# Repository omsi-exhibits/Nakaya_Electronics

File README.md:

# Nakaya Electronics Details

## Theory of Operation
The Nakaya Electronics are composed of a mainboard that a ItsyBitsy32u4 microcontroller is socketed into. The mainboard connects to 4 sensor boards and 4 led light boards. Each Sensor board has 12 reed switches that are read by 2 shift in registers.  Each light board has a 24 rgbw neoPixel ring attached. The software for the microcontroller checks each Sensor board for the snow pucks that correspond as a correct answer to the description of the snow for that section. Each section has 2 answers that work. When a correct answer is placed in the slot the light board fades in a light in the center of the snowflake and the mainboard triggers a sound. When the piece is removed the light fades out.  

The way the software works is that there are Sensor object instances that each loop read the sensor data store it in a data object
and then there is some logic that checks wether or not a correct sensor has been just places or has been just removed. This in turn
calls the led modules trigger functions that begin fading in or fading out.
The same logic is also responsible to trigger sounds
to play when the pieces are inserted or removed. If all 4 of the same type of snowflake are in the correct slots a victory sound will play.

### Updating software
The software is built using platformio. You can use Arduino IDE by copying the src folder
and renaming it to Nakaya and renaming the main.cpp file to Nakaya.ino. This will allow
you to use Arduino to make modifications. You will need to install any missing libraries
through the Arduino Library manager.

### Project File Organization
- docs : documentation and pictures
- src : source code
- eagle : pcb files
- examples_tests : code to help test and trouble shoot
- audio_assets : wavTrigger files
- readme.md : basic project info its the file you are reading
- docs/Nakaya BOM v2.xls (BOM is on sheet 2)
- some other directories are used by platformio and vscode

### Sensor Board
 10” by 10” square board size, sensing distance at 5/8" and less. 
- Shift Register x 2
- Reed Switches
- Phoenix Connectors
- Spacers - Between board and Milkplex
- Stand Offs - Between board and bottom plate

## Main board
- reverse voltage protection
- phoenix connectors
- MCU is Adafruit ItsyBitsy32u4

### Audio 
The wavTrigger is the audio player that interfaces with the main board via a 5pin rectangular connector. KK254 series molex connector.
This connector carries a serial signal over TX and RX lines. The connector also has 5v and gnd to power the board. The wavTrigger needs a pad solder birdged to allow for power intake from the serial input connector.

Software wise an AudioOut object is used to trigger sounds from the main code. It has a private instance of wavTrigger that is the hardware module that
plays wav files. The wavTrigger library has a line un-commented to allow interfacing via the hardware Serial1. The audio files are stereo wav files. 

### Game Pieces
- Each set will have 8 game pucks. Each game puck will have 1 more magnet then the
previous piece. So 1 + 2 +3 +4 +5 +6 +7 +8 = 36 magnets per set.
3 sets total = 108 magnets.
- The sensors count how many magnets are in the game piece to determine what
piece they are. 
- Each Sensor section can have 2 corresponding game pieces that trigger a success animation.

## Shift Registers

74hc165 inputs are enabled by a low level at the shift/load input.
clocking is accomplished by a low-to-high transition of the clock (CLK) input
while SH/LD is held high, and CLK INH is held low. (In my design CLK INH is
tied to ground via a trace)

Parallel load is inhibited when SH/LD is held high. While SH/LD is low the parallel
inputs to the register are enabled.

The SN74HC165 I am using needs clock to pulse from LOW to HIGH. Opposite of arduino
shiftIn().

### The Minimal Viable Product functions
- Scan the sensors every timeStep interval & insert results into DataObject
- Update Data that holds sensor results
- Run logic on Data 
- - If a corresponding puck is detected, Trigger LedModule leds to FadeIn
- - If puck is removed since lastStep Trigger LedModule leds to FadeOut

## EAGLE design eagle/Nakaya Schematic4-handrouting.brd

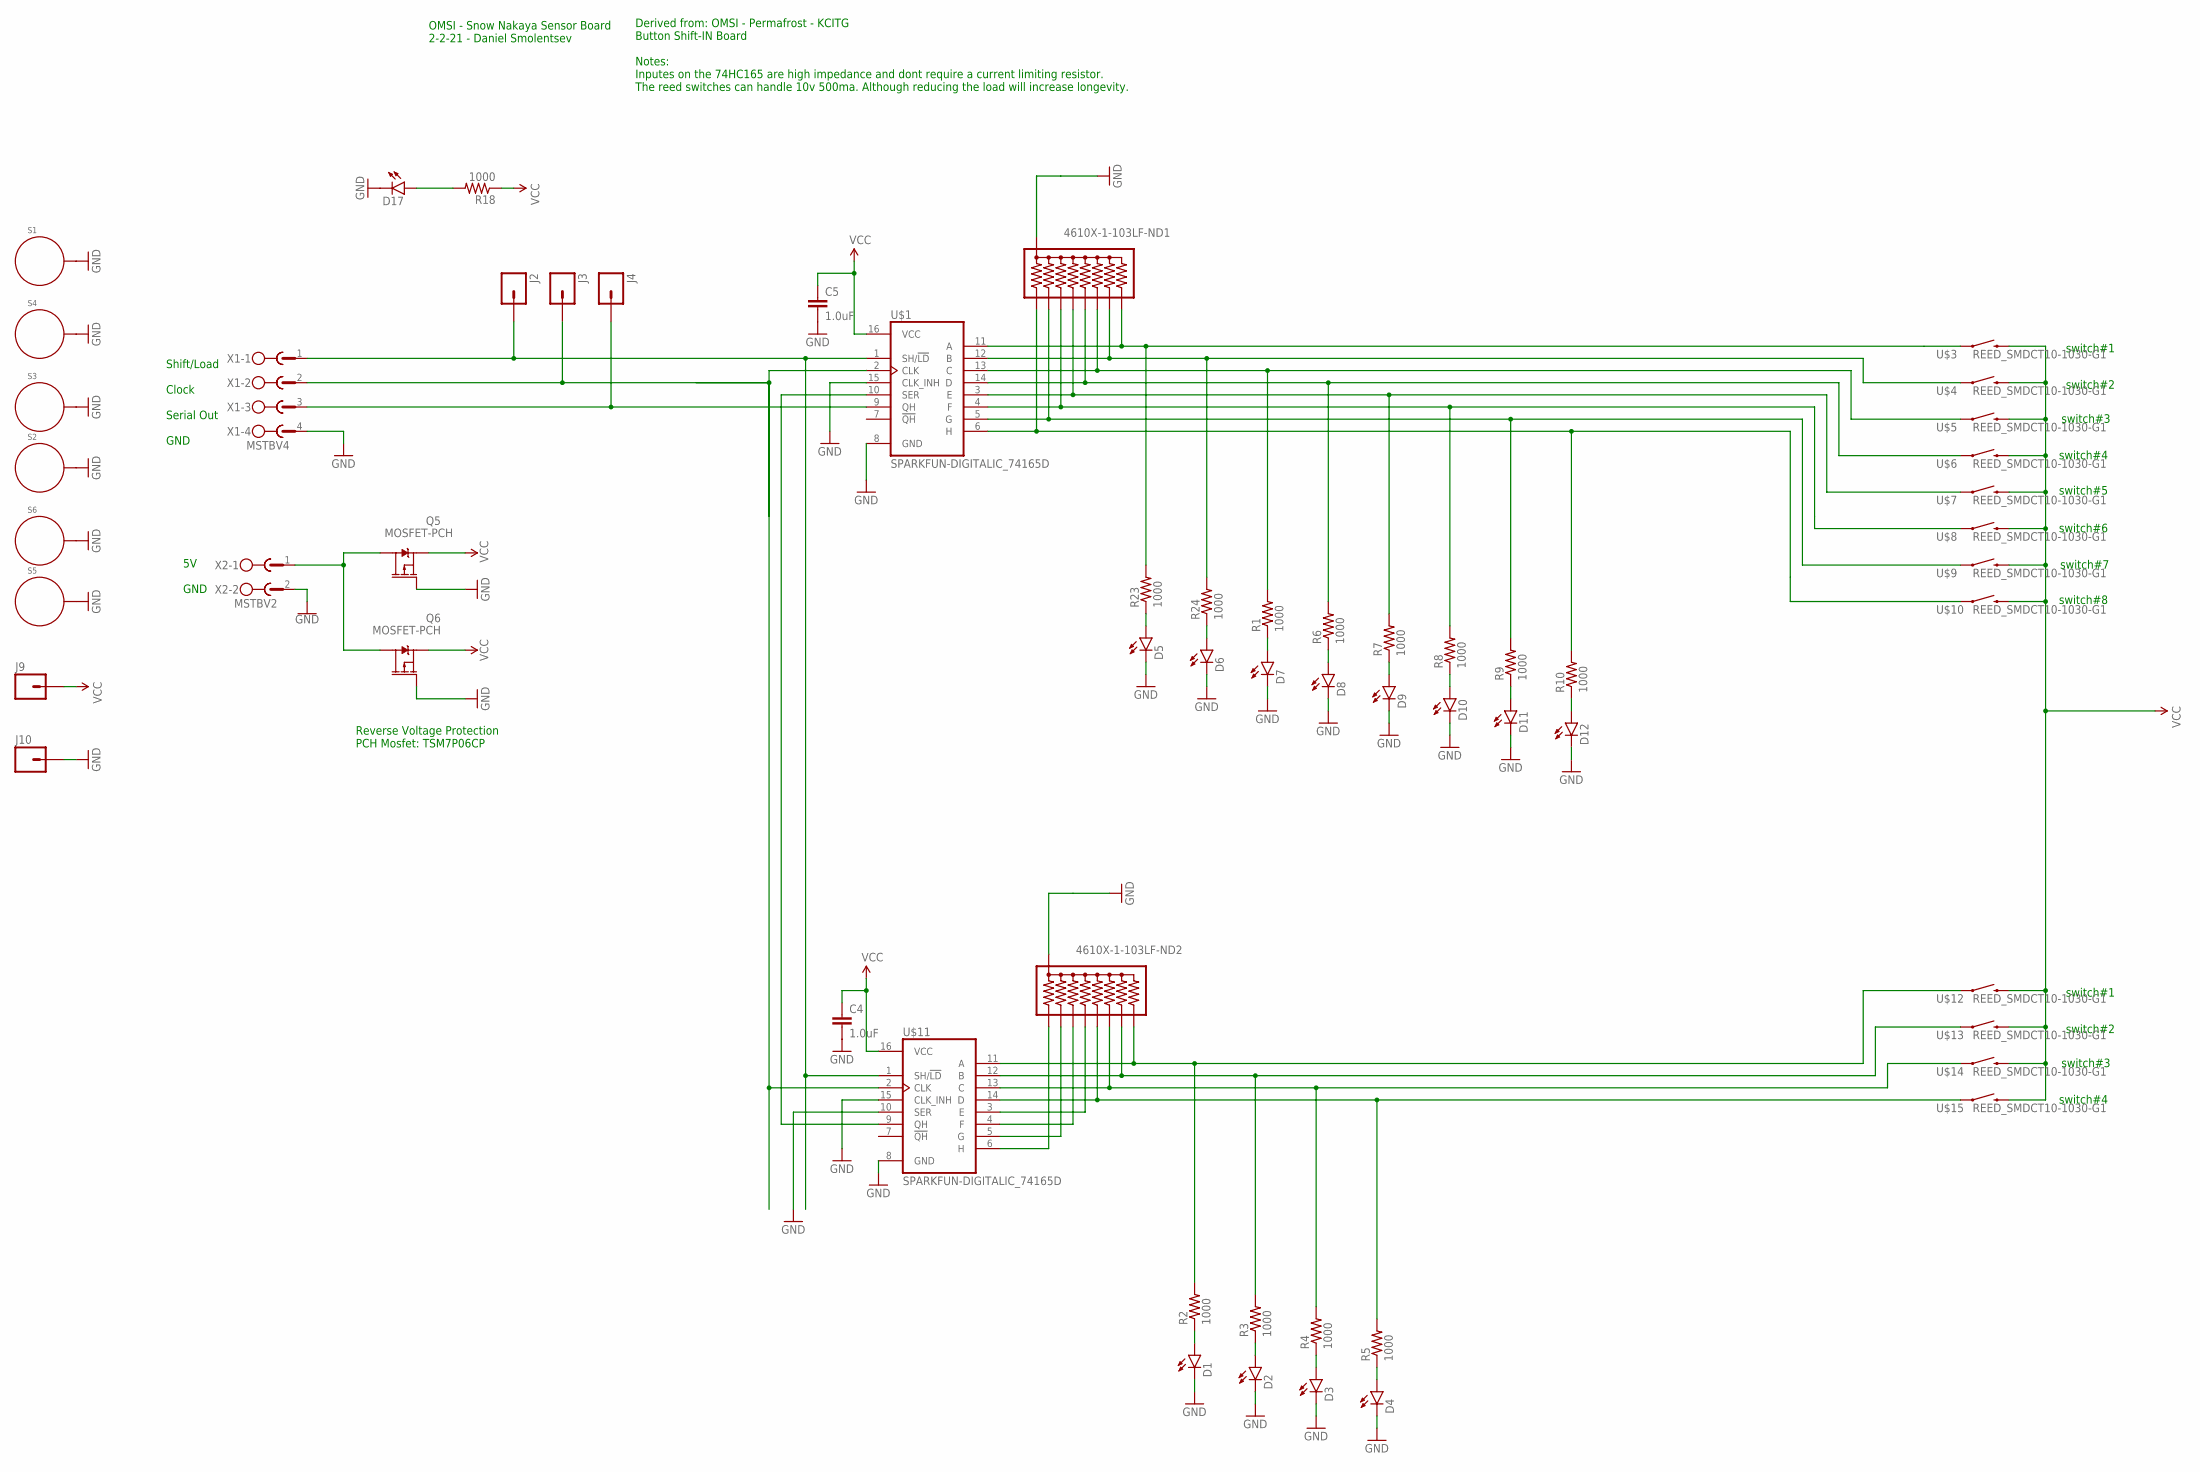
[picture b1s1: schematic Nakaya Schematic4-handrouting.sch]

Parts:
4610X-1-103LF-ND1, 4610X-1-103LF-ND2: RPACK-BUSSED-8-SIP-PTH-8; RPACK-SIP-PTH-8
C4, C5: 1.0uF; SPARKFUN-CAPACITORS_0805
D1, D2, D3, D4, D5, D6, D7, D8, D9, D10, D11, D12, D17: SPARKFUN-LED_LED1206; SPARKFUN-LED_LED-1206
J2, J3, J4, J9, J10: SPARKFUN-CONNECTORS_M01PTH_NO_SILK_YES_STOP; SPARKFUN-CONNECTORS_1X01_NO_SILK
Q5, Q6: MOSFET-PCH; DPAK
R1, R2, R3, R4, R5, R6, R7, R8, R9, R10, R18, R23, R24: 1000; SPARKFUN-PASSIVES_0805:1
S1, S2, S3, S4, S5, S6: STANDOFF_ELECTRICAL.18"; STANDOFF_ELECTRIC_#8_OVERSIZED
U$1, U$11: SPARKFUN-DIGITALIC_74165D; SPARKFUN-DIGITALIC_SO16
U$3, U$4, U$5, U$6, U$7, U$8, U$9, U$10, U$12, U$13, U$14, U$15: REED_SMDCT10-1030-G1; REED_SMD_2
X1: MSTBV4
X2: MSTBV2

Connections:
CLK: J3.1, U$1.2 (CLK), U$11.2 (CLK), X1.2
GND: 4610X-1-103LF-ND1.P$1 (1), 4610X-1-103LF-ND2.P$1 (1), C4.2, C5.2, D1.C, D2.C, D3.C, D4.C, D5.C, D6.C, D7.C, D8.C, D9.C, D10.C, D11.C, D12.C, D17.C, J10.1, Q5.1 (G), Q6.1 (G), S1.P$1, S2.P$1, S3.P$1, S4.P$1, S5.P$1, S6.P$1, U$1.8 (GND), U$1.15 (CLK_INH), U$11.8 (GND), U$11.10 (SER), U$11.15 (CLK_INH), X1.4, X2.2
LD: J2.1, U$1.1 (SH/!LD), U$11.1 (SH/!LD), X1.1
unnamed: 4610X-1-103LF-ND2.P$7 (7), R4.2, U$11.13 (C), U$14.3 (1)
unnamed: 4610X-1-103LF-ND2.P$6 (6), R5.2, U$11.14 (D), U$15.3 (1)
unnamed: D17.A, R18.2
unnamed: 4610X-1-103LF-ND1.P$4 (4), R8.2, U$1.4 (F), U$8.3 (1)
unnamed: Q5.4 (D), Q6.4 (D), X2.1
unnamed: 4610X-1-103LF-ND1.P$3 (3), R9.2, U$1.5 (G), U$9.3 (1)
unnamed: 4610X-1-103LF-ND1.P$2 (2), R10.2, U$1.6 (H), U$10.3 (1)
unnamed: D5.A, R23.1
unnamed: 4610X-1-103LF-ND2.P$8 (8), R3.2, U$11.12 (B), U$13.3 (1)
unnamed: D7.A, R1.1
unnamed: D6.A, R24.1
unnamed: D1.A, R2.1
unnamed: D8.A, R6.1
unnamed: D2.A, R3.1
unnamed: 4610X-1-103LF-ND2.P$9 (9), R2.2, U$11.11 (A), U$12.3 (1)
unnamed: D3.A, R4.1
unnamed: D4.A, R5.1
unnamed: D9.A, R7.1
unnamed: 4610X-1-103LF-ND2.P$5 (5), U$11.3 (E)
unnamed: 4610X-1-103LF-ND2.P$4 (4), U$11.4 (F)
unnamed: 4610X-1-103LF-ND2.P$3 (3), U$11.5 (G)
unnamed: D10.A, R8.1
unnamed: 4610X-1-103LF-ND2.P$2 (2), U$11.6 (H)
unnamed: D11.A, R9.1
unnamed: D12.A, R10.1
unnamed: 4610X-1-103LF-ND1.P$9 (9), R23.2, U$1.11 (A), U$3.3 (1)
unnamed: 4610X-1-103LF-ND1.P$8 (8), R24.2, U$1.12 (B), U$4.3 (1)
unnamed: 4610X-1-103LF-ND1.P$7 (7), R1.2, U$1.13 (C), U$5.3 (1)
unnamed: 4610X-1-103LF-ND1.P$6 (6), R6.2, U$1.14 (D), U$6.3 (1)
unnamed: 4610X-1-103LF-ND1.P$5 (5), R7.2, U$1.3 (E), U$7.3 (1)
QH: J4.1, U$1.9 (QH), X1.3
SER: U$1.10 (SER), U$11.9 (QH)
VCC: C4.1, C5.1, J9.1, Q5.3 (S), Q6.3 (S), R18.1, U$1.16 (VCC), U$3.4 (2), U$4.4 (2), U$5.4 (2), U$6.4 (2), U$7.4 (2), U$8.4 (2), U$9.4 (2), U$10.4 (2), U$11.16 (VCC), U$12.4 (2), U$13.4 (2), U$14.4 (2), U$15.4 (2)

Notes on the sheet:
Derived from: OMSI - Permafrost - KCITG Button Shift-IN Board Notes: Inputes on the 74HC165 are high impedance and dont require a current limiting resistor. The reed switches can handle 10v 500ma. Although reducing the load will increase longevity.
switch#1
switch#2
switch#3
switch#4
switch#5
switch#6
switch#7
switch#8
Shift/Load Clock Serial Out GND
Reverse Voltage Protection PCH Mosfet: TSM7P06CP
5V GND
OMSI - Snow Nakaya Sensor Board 2-2-21 - Daniel Smolentsev

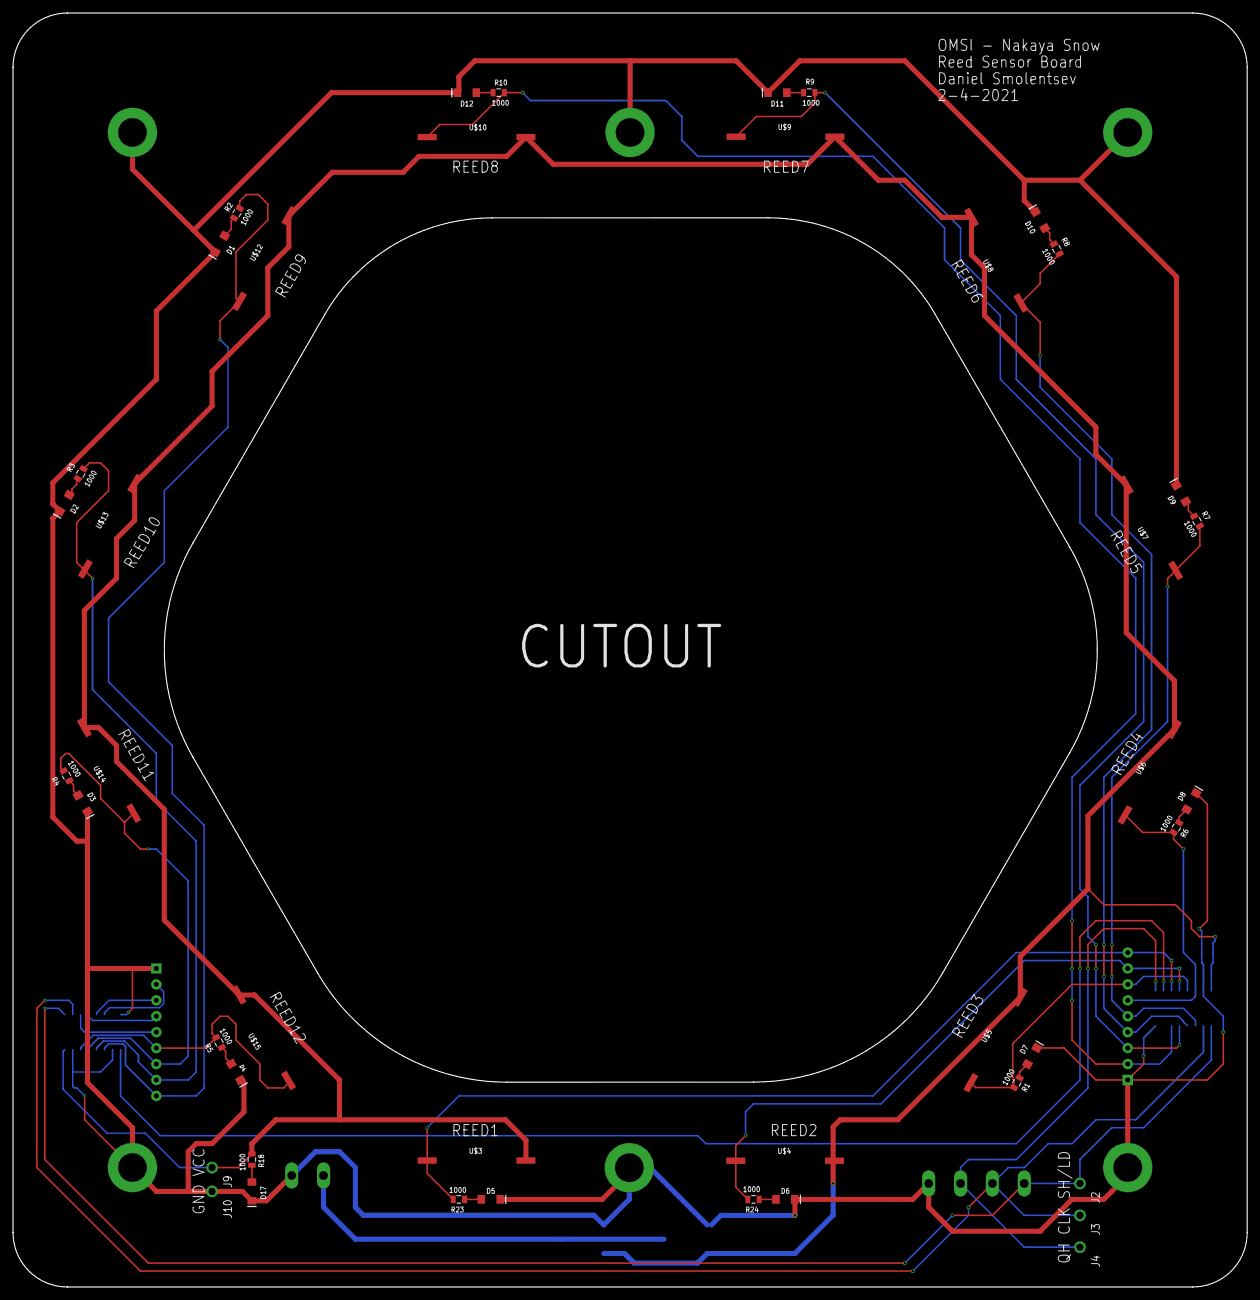
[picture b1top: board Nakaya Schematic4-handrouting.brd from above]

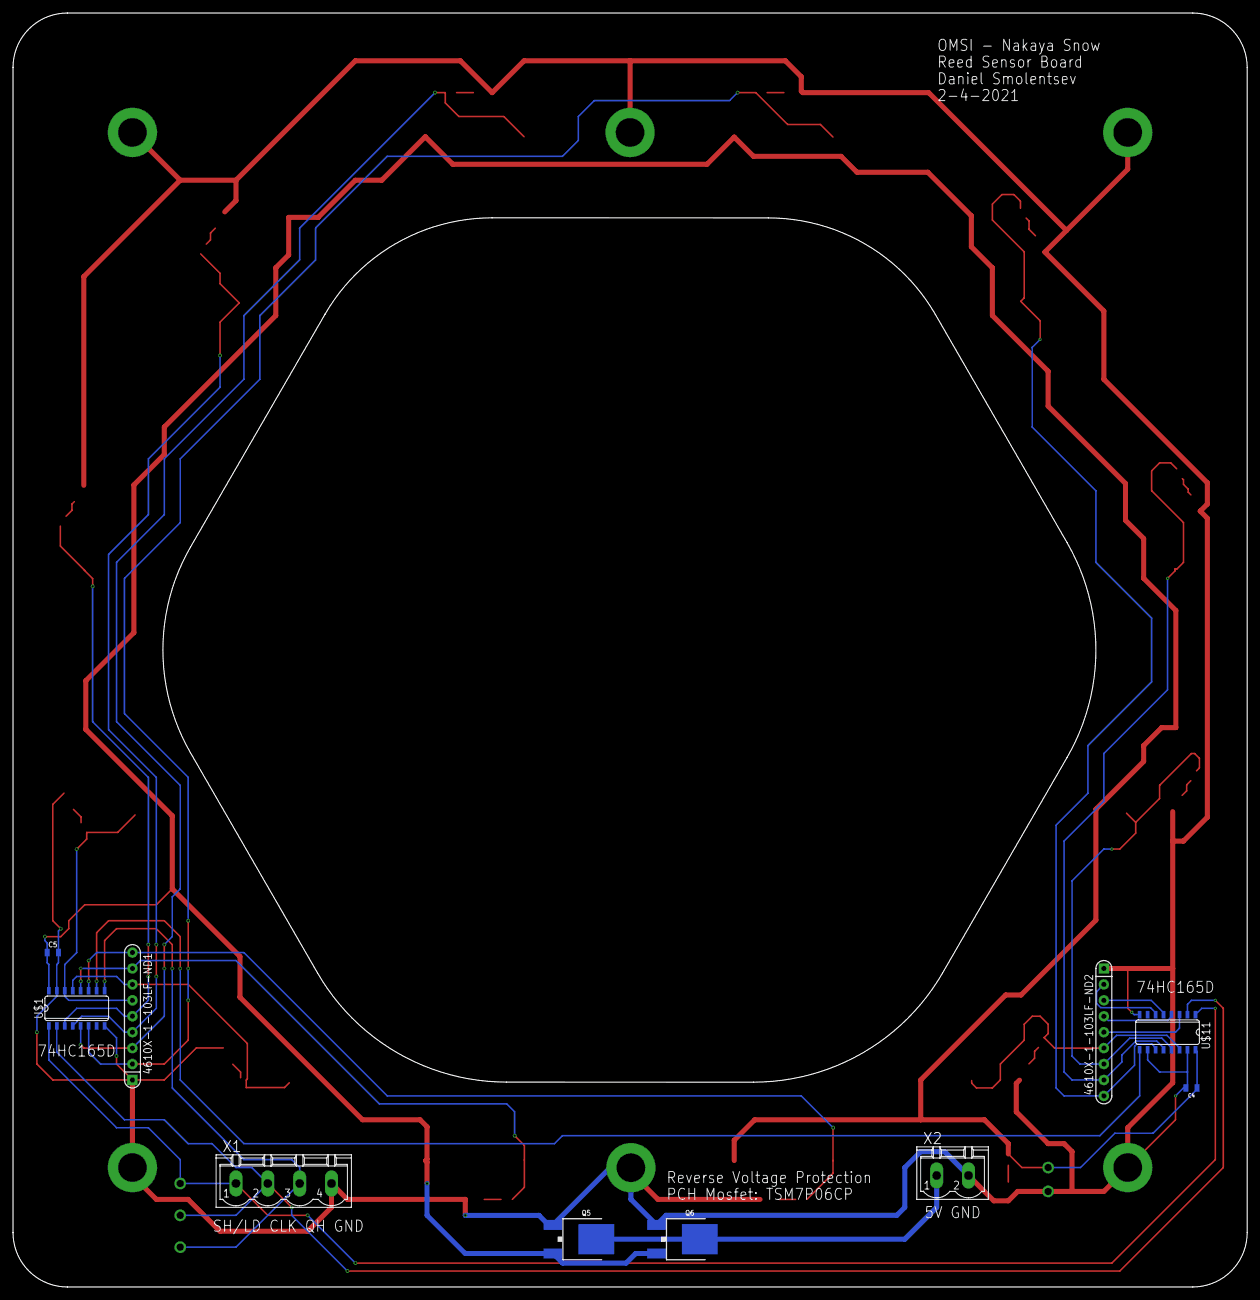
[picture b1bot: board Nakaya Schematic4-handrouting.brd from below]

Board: 2 copper layers, 196.8 x 203.2 mm, 59 parts (10 on the bottom side), 36 nets.

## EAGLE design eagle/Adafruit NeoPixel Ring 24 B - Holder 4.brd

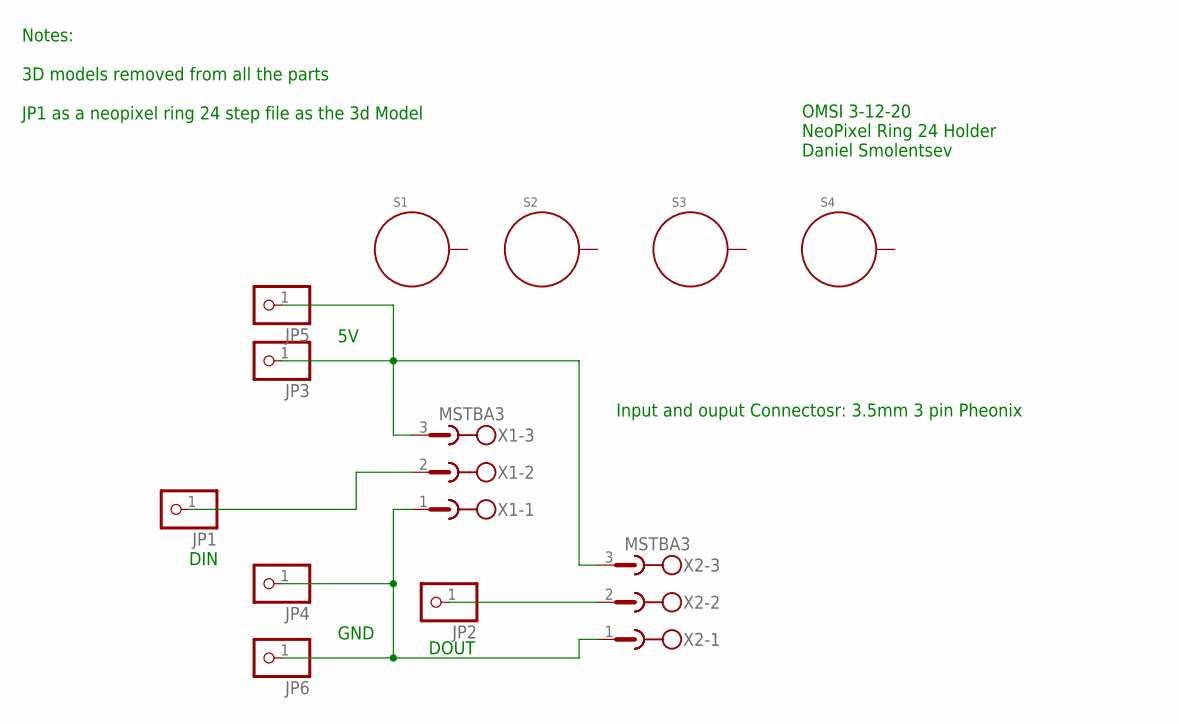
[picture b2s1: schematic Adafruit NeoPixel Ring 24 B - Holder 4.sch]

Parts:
JP1, JP2, JP3, JP4, JP5, JP6: PINHD-1X1CB; 1X01-CLEANBIG
S1, S2, S3, S4: STANDOFF_ELECTRICAL.17"; STANDOFF-ELECTRICAL
X1, X2: MSTBA3

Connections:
5V: JP3.1, JP5.1, X1.3, X2.3
DIN: JP1.1, X1.2
GND: JP4.1, JP6.1, X1.1, X2.1
unnamed: JP2.1, X2.2

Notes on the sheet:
GND
DIN
DOUT
Input and ouput Connectosr: 3.5mm 3 pin Pheonix
OMSI 3-12-20 NeoPixel Ring 24 Holder Daniel Smolentsev
Notes: 3D models removed from all the parts JP1 as a neopixel ring 24 step file as the 3d Model

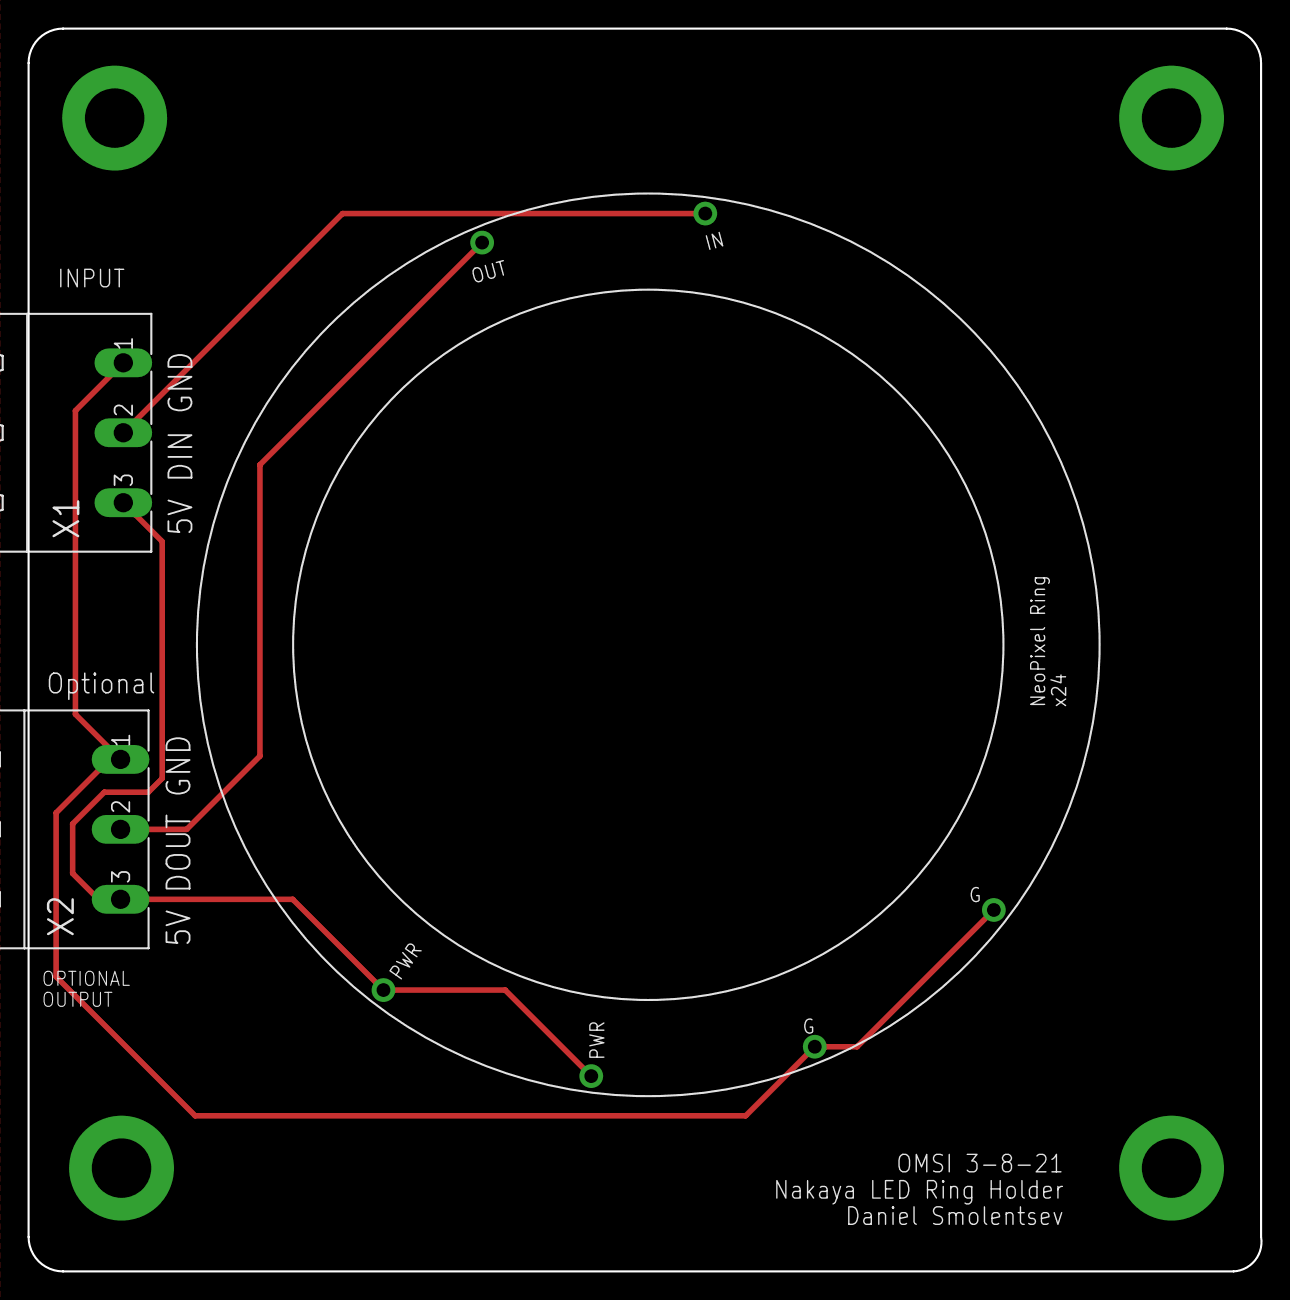
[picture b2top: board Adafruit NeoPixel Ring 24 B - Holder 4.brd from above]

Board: 2 copper layers, 89.5 x 90.2 mm, 12 parts (0 on the bottom side), 4 nets.

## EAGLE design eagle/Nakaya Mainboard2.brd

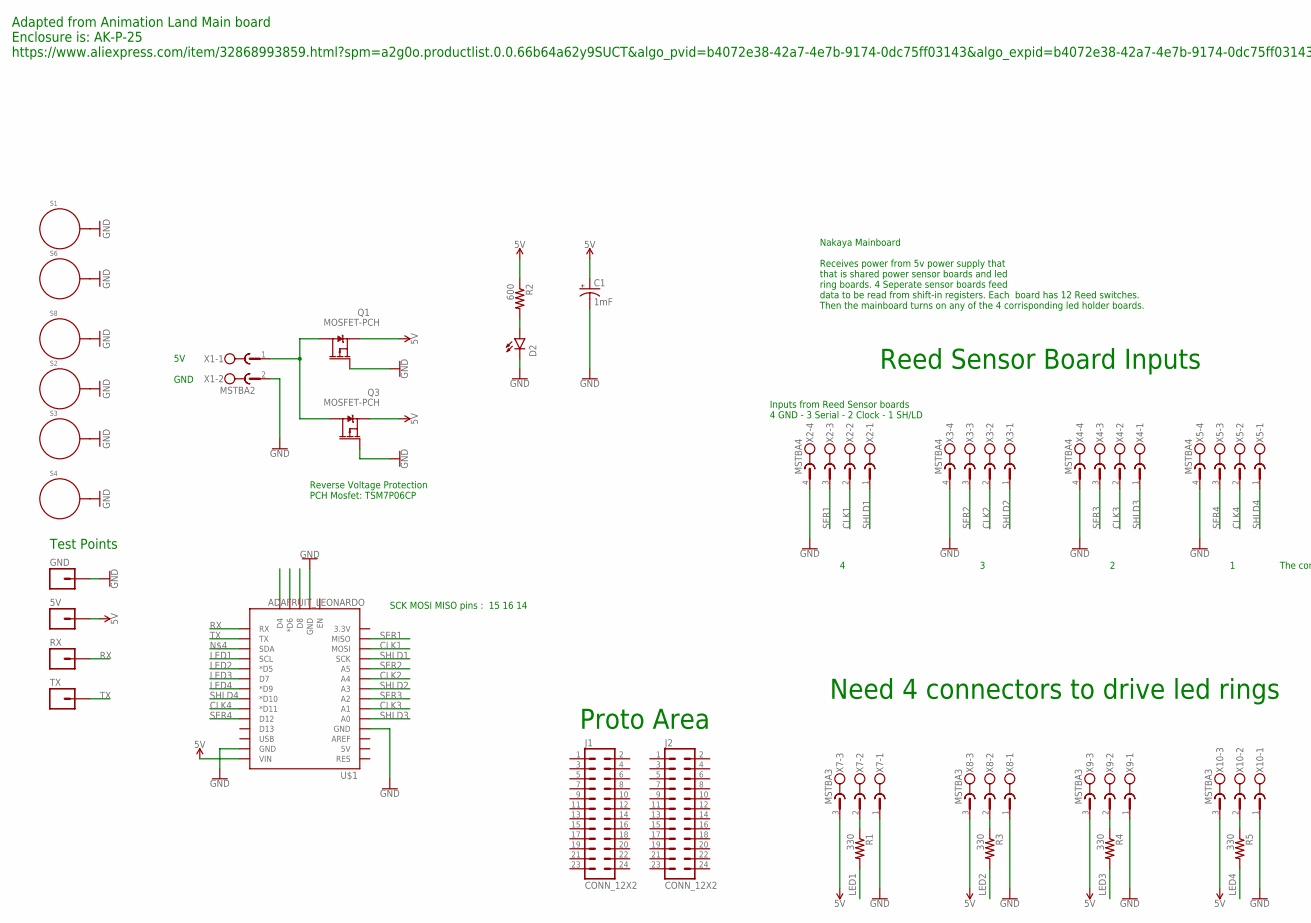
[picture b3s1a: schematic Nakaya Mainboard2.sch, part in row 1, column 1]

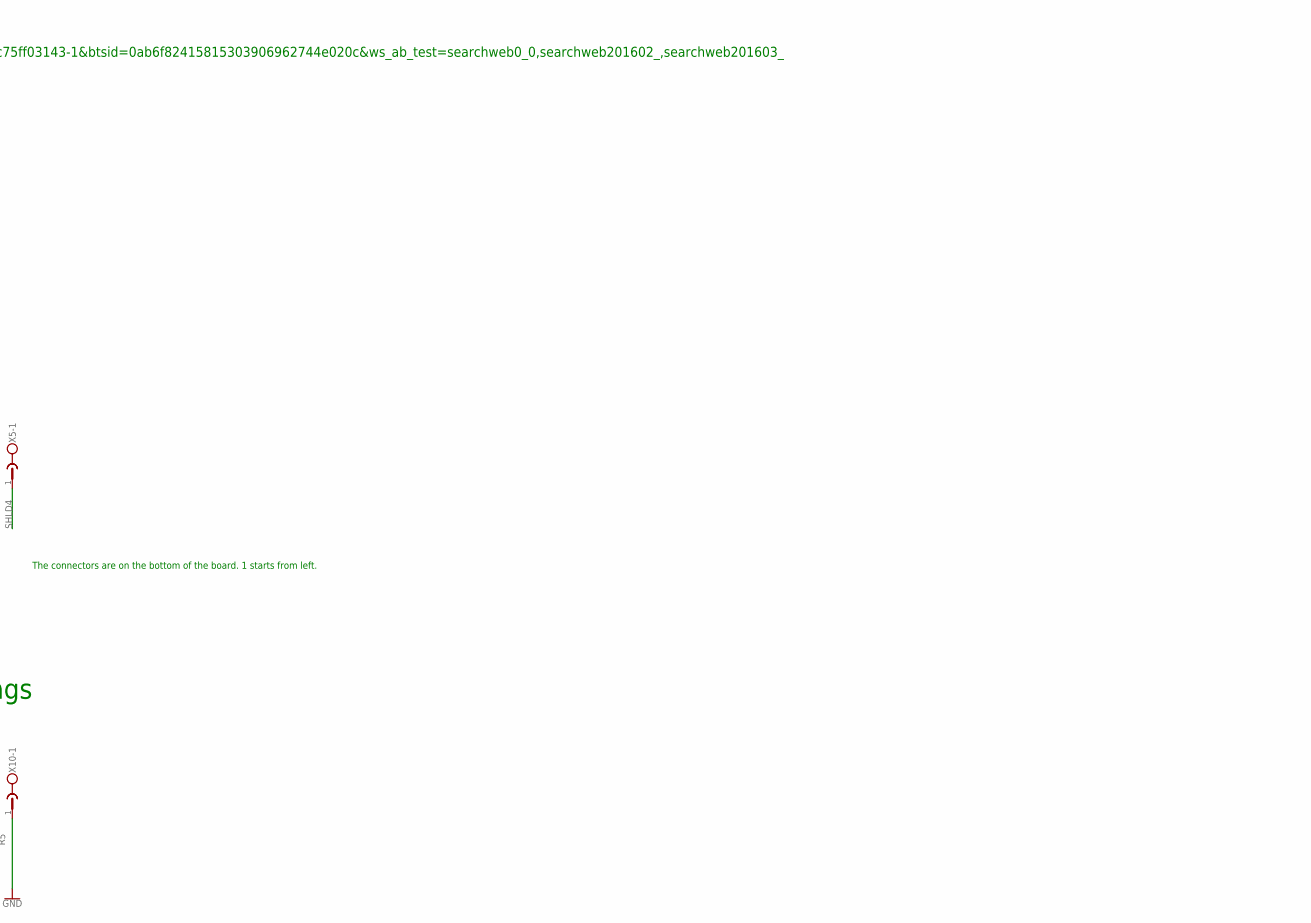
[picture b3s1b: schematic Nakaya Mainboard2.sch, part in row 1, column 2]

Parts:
5V: M01PTH; 1X01
C1: 1mF; CPOL-RADIAL-5MM-10MM
D2: RED; SPARKFUN-LED_LED-1206
GND: M01PTH; 1X01
J1, J2: CONN_12X2; 2X12
Q1, Q3: MOSFET-PCH; DPAK
R1, R3, R4, R5: 330; R0805
R2: 600; R0805
RX: M01PTH; 1X01
S1, S2, S3, S4, S6, S8: STANDOFF_ELECTRICAL5-32; STANDOFF_ELECTRICAL_5_32
TX: M01PTH; 1X01
U$1: ADAFRUIT_LEONARDO; ADAFRUIT_LENOARDO
X1: MSTBA2
X2, X3, X4, X5: MSTBA4
X7, X8, X9, X10: MSTBA3

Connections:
5V: 5V.1, C1.+, Q1.3 (S), Q3.3 (S), R2.1, U$1.VIN, X7.3, X8.3, X9.3, X10.3
CLK1: U$1.MOSI, X2.2
CLK2: U$1.A4, X3.2
CLK3: U$1.A1, X4.2
CLK4: U$1.D11 (*D11), X5.2
GND: C1.-, D2.C, GND.1, Q1.1 (G), Q3.1 (G), S1.P1, S2.P1, S3.P1, S4.P1, S6.P1, S8.P1, U$1.GND@0 (GND), U$1.GND@1 (GND), U$1.GND@2 (GND), X1.2, X2.4, X3.4, X4.4, X5.4, X7.1, X8.1, X9.1, X10.1
LED1: R1.2, U$1.SCL
LED2: R3.2, U$1.D5 (*D5)
LED3: R4.2, U$1.D7
LED4: R5.2, U$1.D9 (*D9)
unnamed: D2.A, R2.2
unnamed: R1.1, X7.2
unnamed: R3.1, X8.2
unnamed: R4.1, X9.2
unnamed: R5.1, X10.2
unnamed: Q1.4 (D), Q3.4 (D), X1.1
RX: RX.1, U$1.RX
SER1: U$1.MISO, X2.3
SER2: U$1.A5, X3.3
SER3: U$1.A2, X4.3
SER4: U$1.D12, X5.3
SHLD1: U$1.SCK, X2.1
SHLD2: U$1.A3, X3.1
SHLD3: U$1.A0, X4.1
SHLD4: U$1.D10 (*D10), X5.1
TX: TX.1, U$1.TX

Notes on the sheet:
Adapted from Animation Land Main board Enclosure is: AK-P-25 https://www.aliexpress.com/item/32868993859.html?spm=a2g0o.productlist.0.0.66b64a62y9SUCT&algo_pvid=b4072e38-42a7-4e7b-9174-0dc75ff03143&algo_expid=b4072e38-42a7-4e7b-9174-0dc75ff03143-1&btsid=0ab6f82415815303906962744e020c&ws_ab_test=sea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
Nakaya Mainboard Receives power from 5v power supply that that is shared power sensor boards and led ring boards. 4 Seperate sensor boards feed data to be read from shift-in registers. Each board has 12 Reed switches. Then the mainboard turns on any of the 4 corrisponding led holder boards.
Reverse Voltage Protection PCH Mosfet: TSM7P06CP
Inputs from Reed Sensor boards 4 GND - 3 Serial - 2 Clock - 1 SH/LD
5V GND
Need 4 connectors to drive led rings
Reed Sensor Board Inputs
SCK MOSI MISO pins : 15 16 14
Proto Area
Test Points
The connectors are on the bottom of the board. 1 starts from left.

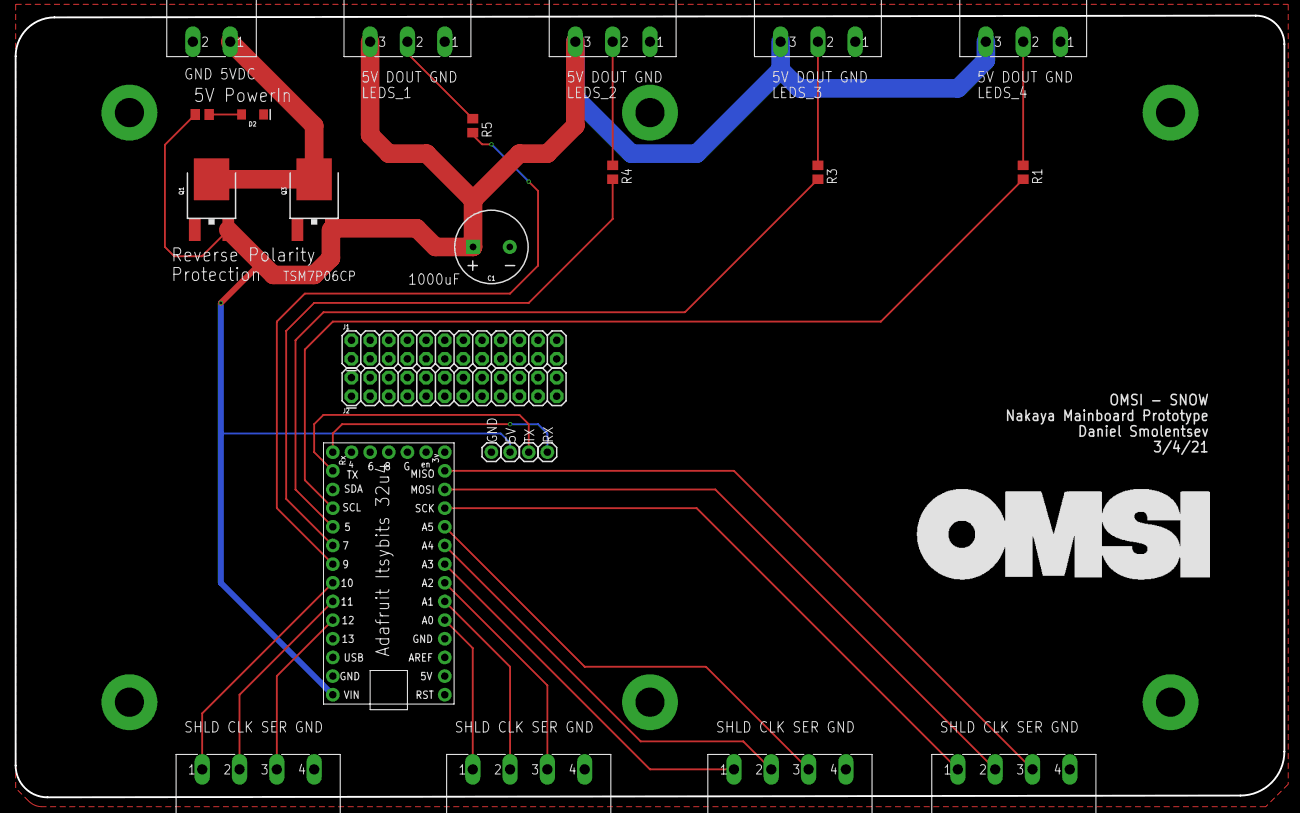
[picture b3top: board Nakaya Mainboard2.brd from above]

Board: 2 copper layers, 172.7 x 106.4 mm, 31 parts (0 on the bottom side), 26 nets.

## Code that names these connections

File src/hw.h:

#ifndef HW_H
#define HW_H

#define SER1 14
#define CLK1 16
#define SHLD1 15

#define SER2 A5
#define CLK2 A4
#define SHLD2 A3

#define SER3 A2
#define CLK3 A1
#define SHLD3 A0

#define SER4 12
#define CLK4 11
#define SHLD4 10

#define LEDPIN1 9
#define LEDPIN2 7
#define LEDPIN3 5
#define LEDPIN4 3
#define NUMLEDS 24

#define HEARTLED 13

#endif

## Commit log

2021-05-03 very basic senseing of a 2 magnet on 1 puckSensor. Lights up Leds too
2021-05-12 Basic MVP is working
2021-05-13 The Version 1 Code is complete
2021-05-13 Updates Branched
2021-07-21 added wavTrigger and AudioOut support
2021-08-02 Basic MVP audio is working well. Retrigger delay timers are in place
2021-08-25 This is a Release candidate! Added victory sounds, cleaned up
2021-08-25 Added in all the docs, pictures, eagle, assets, into this repo
2022-06-16 updated docs, added tech manual, removed duplicate info

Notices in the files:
parts and their libraries:
microbuilder: This work is placed in the public domain, and may be freely used for commercial and non-commercial work with the following conditions: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
SparkFun-Connectors: Licensing: Creative Commons ShareAlike 4.0 International - https://creativecommons.org/licenses/by-sa/4.0
